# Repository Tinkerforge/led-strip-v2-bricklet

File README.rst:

LED Strip Bricklet 2.0
======================

This repository contains the firmware source code and the hardware design
files. The documentation generator configs can be found at
https://github.com/Tinkerforge/generators

Repository Content
------------------

software/:
 * examples/: Examples for all supported languages
 * build/: Compiled files
 * src/: Source code of firmware
 * Makefile: Makefile to build project

hardware/:
 * Contains KiCad project files and additionally schematics as PDF

datasheets/:
 * Contains datasheets for sensors and complex ICs that are used

Hardware
--------

The hardware is designed with the open source EDA Suite KiCad
(http://www.kicad.org). Before you are able to open the files,
you have to install the Tinkerforge kicad-libraries
(https://github.com/Tinkerforge/kicad-libraries). You can either clone
them directly in hardware/ or clone them in a separate folder and
symlink them into hardware/
(ln -s kicad_path/kicad-libraries project_path/hardware). After that you
can open the .pro file in hardware/ with KiCad and from there view and
modify the schematics and the PCB layout.

Software
--------

If you want to do your own Brick/Bricklet firmware development we highly
recommend that you use our build environment setup script and read the
tutorial (https://www.tinkerforge.com/en/doc/Tutorials/Tutorial_Build_Environment/Tutorial.html).

To compile the C code we recommend you to install the newest GNU Arm Embedded
Toolchain (https://launchpad.net/gcc-arm-embedded/+download).
You also need to install bricklib2 (https://github.com/Tinkerforge/bricklib2).

You can either clone it directly in software/src/ or clone it in a
separate folder and symlink it into software/src/
(ln -s bricklib_path/bricklib2 project_path/software/src/). Finally make sure to
have CMake installed (http://www.cmake.org/cmake/resources/software.html).

After that you can build the firmware by invoking make in software/.
The firmware (.zbin) can then be found in software/build/ and uploaded
with brickv (click button "Flashing" on start screen).

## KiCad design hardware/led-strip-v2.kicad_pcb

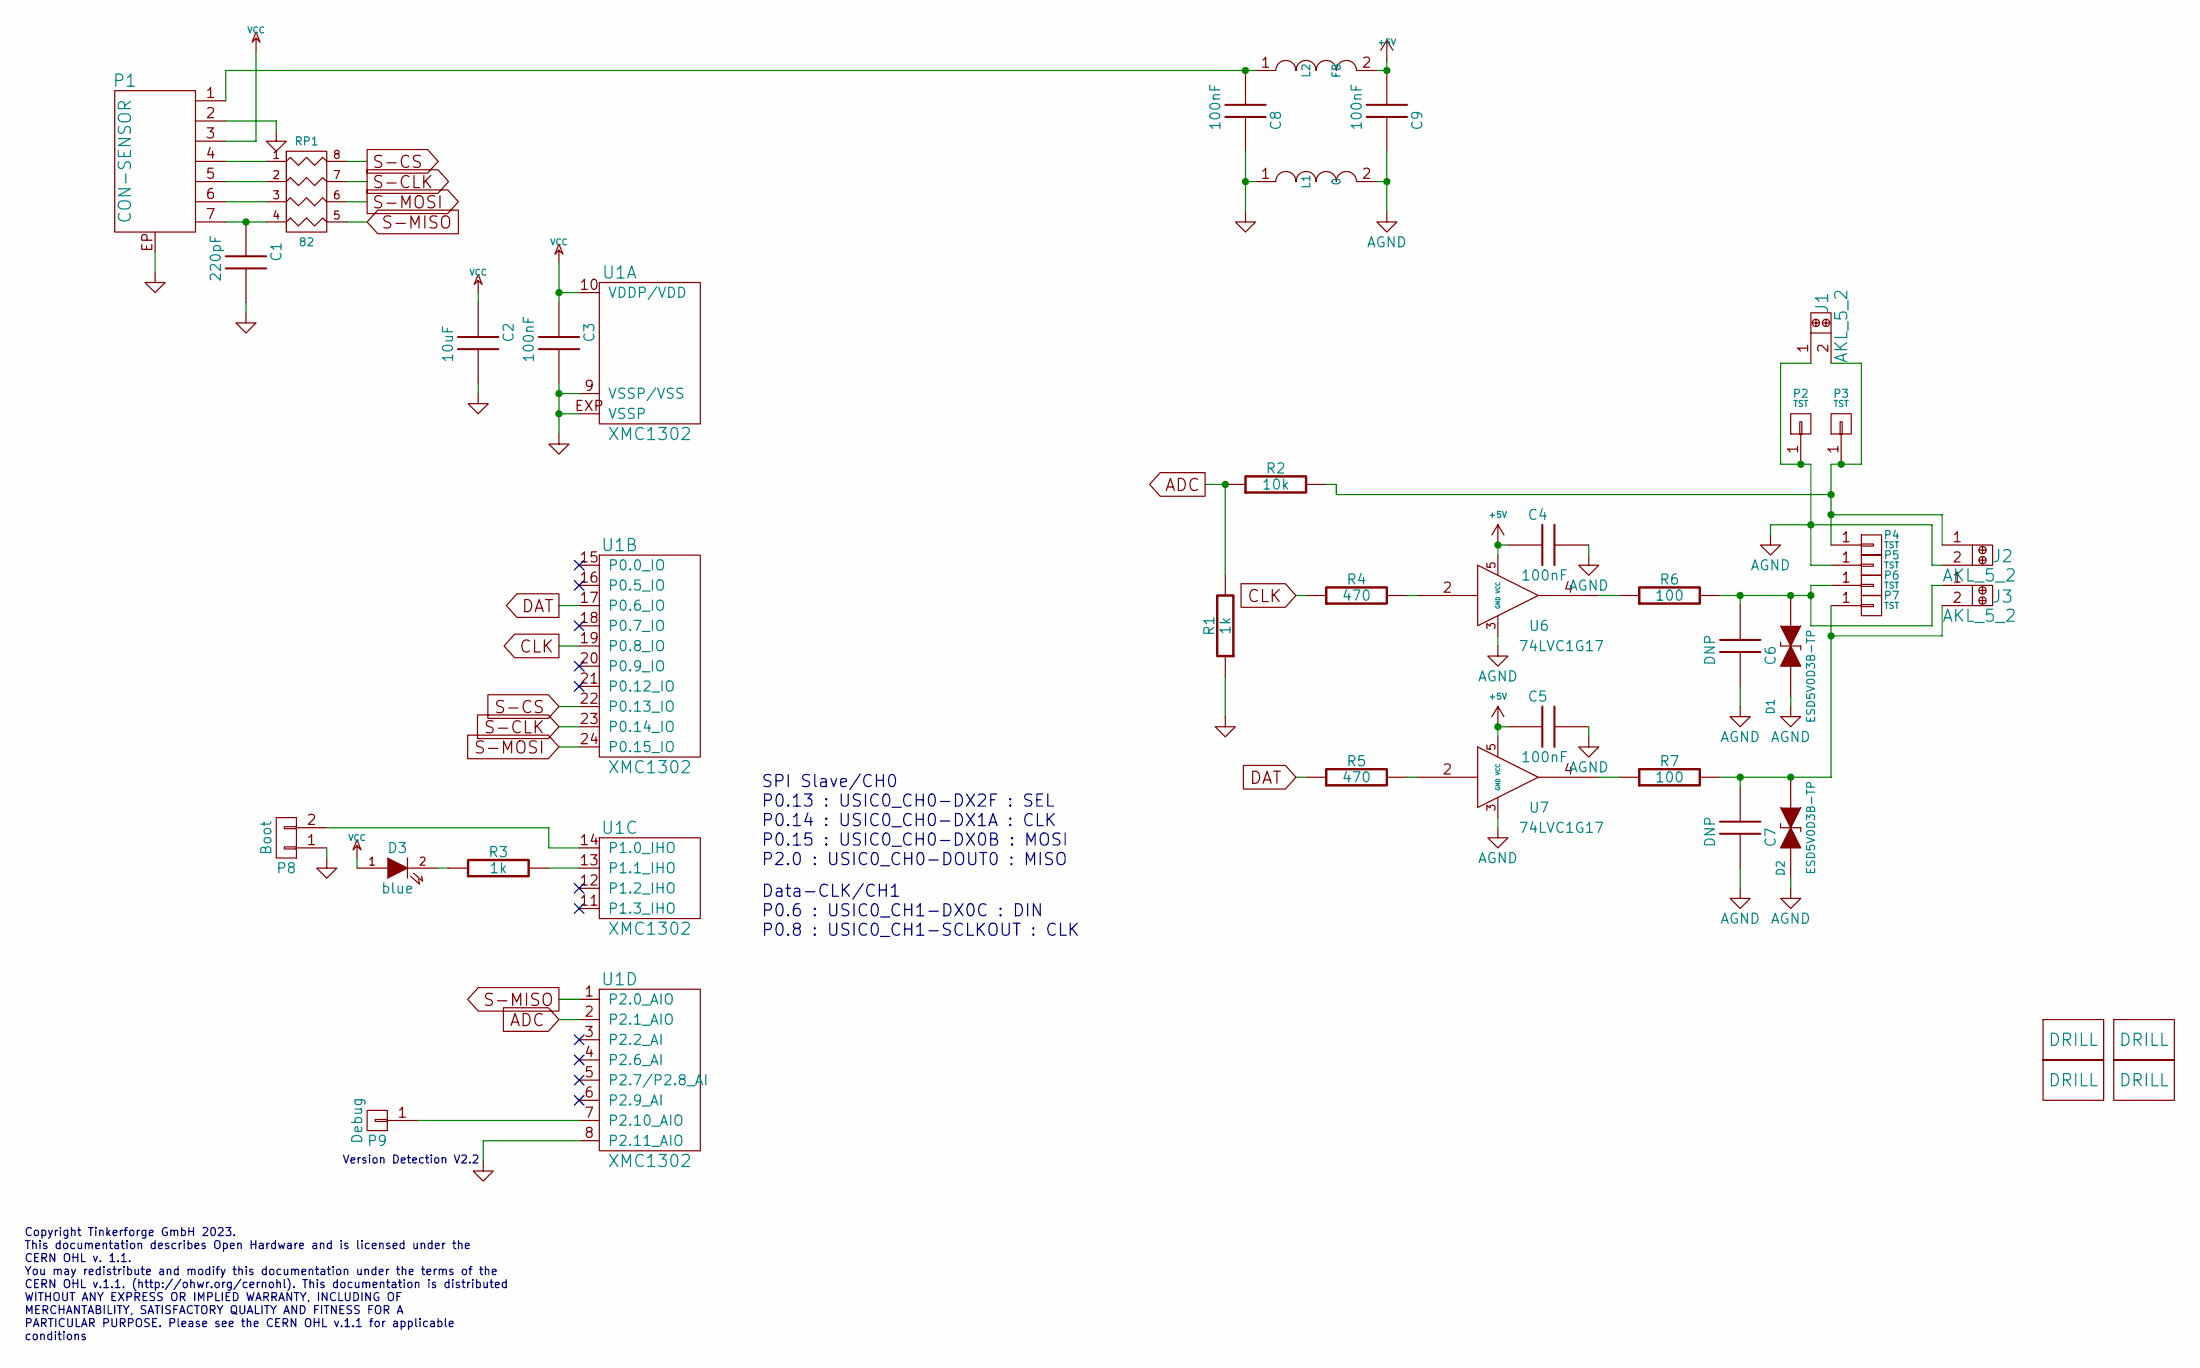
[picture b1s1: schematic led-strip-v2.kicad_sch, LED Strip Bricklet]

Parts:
C1: 220pF; C0402F
C2: 10uF; C0805E
C3, C4, C5, C8, C9: 100nF; C0603F
C6, C7: DNP; C0603F
D1, D2: ESD5V0D3B-TP; SOD-323
D3: blue; D0603F
J1, J2, J3: AKL_5_2
L1: 0; R0603F
L2: FB; R0603F
P1: CON-SENSOR; CON-SENSOR2
P2, P3, P4, P5, P6, P7: TST; SOLDER_PAD2
P8: Boot; SolderJumper
P9: Debug; DEBUG_PAD
R1, R3: 1k; R0603F
R2: 10k; R0603F
R4, R5: 470; R0603F
R6, R7: 100; R0603F
RP1: 82; 4X0402
U1: XMC1302; QFN24-4x4mm-0.5mm
U2, U3, U4, U5: DRILL; DRILL_NP
U6, U7: 74LVC1G17; SOT23-5

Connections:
+5V: C4.1, C5.1, C9.1, L2.2, U6.5 (VCC), U7.5 (VCC)
ADC: R1.2, R2.1, U1.2 (P2.1_AIO)
AGND: C4.2, C5.2, C6.2, C7.2, C9.2, D1.2 (K), D2.2 (K), J1.1, J2.2, L1.2, P2.1, P5.1, U6.3 (GND), U7.3 (GND)
CLK: R4.1, U1.19 (P0.8_IO)
DAT: R5.1, U1.17 (P0.6_IO)
GND: C1.2, C2.2, C3.2, C8.2, L1.1, P1.2, P1.EP, P8.1, R1.1, U1.8 (P2.11_AIO), U1.9 (VSSP/VSS), U1.EXP (VSSP)
unnamed: C1.1, P1.7, RP1.4
unnamed: C6.1, D1.1 (A), J3.1, P6.1, R6.2
unnamed: C7.1, D2.1 (A), J3.2, P7.1, R7.2
unnamed: C8.1, L2.1, P1.1
unnamed: D3.2 (K), R3.1
unnamed: J1.2, J2.1, P3.1, P4.1, R2.2
unnamed: P1.4, RP1.1
unnamed: P1.5, RP1.2
unnamed: P1.6, RP1.3
unnamed: P8.2, U1.14 (P1.0_IHO)
unnamed: P9.1, U1.7 (P2.10_AIO)
unnamed: R3.2, U1.13 (P1.1_IHO)
unnamed: R4.2, U6.2
unnamed: R5.2, U7.2
unnamed: R6.1, U6.4
unnamed: R7.1, U7.4
S-CLK: RP1.7 (R2), U1.23 (P0.14_IO)
S-CS: RP1.8 (R1), U1.22 (P0.13_IO)
S-MISO: RP1.5 (R4), U1.1 (P2.0_AIO)
S-MOSI: RP1.6 (R3), U1.24 (P0.15_IO)
VCC: C2.1, C3.1, D3.1 (A), P1.3, U1.10 (VDDP/VDD)

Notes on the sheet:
Copyright Tinkerforge GmbH 2023. This documentation describes Open Hardware and is licensed under the CERN OHL v. 1.1. You may redistribute and modify this documentation under the terms of the CERN OHL v.1.1. (http://ohwr.org/cernohl). This documentation is distributed WITHOUT ANY EXPRESS OR IMPLIE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
Version Detection V2.2
SPI Slave/CH0 P0.13 : USIC0_CH0-DX2F : SEL P0.14 : USIC0_CH0-DX1A : CLK P0.15 : USIC0_CH0-DX0B : MOSI P2.0 : USIC0_CH0-DOUT0 : MISO
Data-CLK/CH1 P0.6 : USIC0_CH1-DX0C : DIN P0.8 : USIC0_CH1-SCLKOUT : CLK

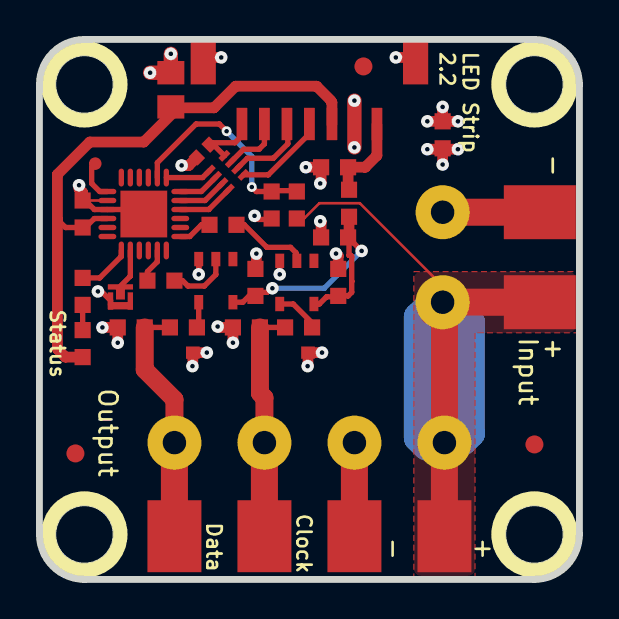
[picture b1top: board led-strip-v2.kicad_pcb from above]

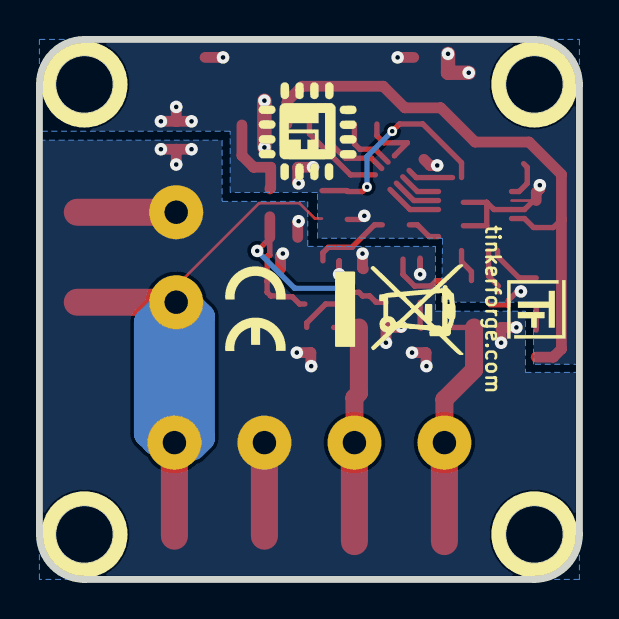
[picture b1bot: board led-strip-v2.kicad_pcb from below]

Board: 2 copper layers, 30.0 x 30.0 mm, 46 parts (2 on the bottom side), 27 nets.

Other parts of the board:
Fiducial_Mark: VAL**; Fiducial_Mark
Fiducial_Mark#2, Fiducial_Mark#3: VAL**; Fiducial_Mark
VAL: CE_5mm
VAL#2: WEEE_7mm

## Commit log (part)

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2018-01-11 add readme file
2018-01-12 add new hardware prototype
2018-01-15 change default via size
2018-02-15 specify processor
2018-02-15 Add datasheets
2018-02-15 Add gitignore
2018-02-15 Add firmware
2018-02-20 Cleanup KiCad libraries config
    Ensure LibDir=kicad-libraries and LibName1=tinkerforge.
    Remove special library.
2018-03-05 Remove unused flash-size define
2018-03-15 fix description text
2018-03-26 Make sure that LED type is updated during initialization
2018-04-16 Add 3d model (*.FCStd & *.step)
2018-05-04 Rename files
2018-05-04 Add schematic PDF
2018-05-30 remove solder paste layer of solder pads
2018-05-30 Add examples skeletons
2018-06-04 Fix get_values streaming logic
2018-06-04 Remove debug
2018-06-07 Fix indentation
2018-06-07 Update changelog for initial release
2018-06-11 Fix bit mixup in lookup table for WS281x LEDs
2018-06-13 Fix schematic filename
2018-06-18 Change capacitor footprint(s) to C0402F
2018-06-28 Fix readme
2018-07-11 Add Makefile with docker support
2018-07-11 Update directory structure and build instructions
2018-07-11 Remove obsolete generate_makefile scripts
2018-07-17 examples: Fix wrong callback name
2018-07-19 Fix typo
2018-10-04 Increase version for new release (changes in bricklib2)
2018-10-04 Add rev to changelog
2018-11-06 Add rust examples
2018-11-07 rust: Accept host names for ip connection, fix naming inconsistencies
2018-11-07 rust: Rename callback receivers.
2018-11-12 Fill in incomplete LED Strip V2 Python examples
2018-11-12 Add auto-generated simple examples
2018-11-28 c: Add missing stream length parameter
2018-12-14 Add go examples.
2018-12-18 go: Change import path.
2018-12-18 go: Change import path again.
2018-12-20 rust: Fix result variable names in examples.
2019-01-24 mqtt: Add examples.
2019-01-24 mqtt: Fix example header.
2019-01-24 mqtt: Remove executable bit in example permissions.
2019-01-24 go: Minor example fixes.
2019-03-28 mqtt: Fix whitespace.
2019-03-28 c: Examples: Pre-declare array used as parameter.
2019-05-14 Update rust examples.
2019-05-29 Dont disable post calibration
2019-08-22 c: Adapt to bindings changes
2019-11-20 Rewrite get_led_values. Fix streaming.
2019-11-20 Increase version for new release.
2019-11-20 Add rev to changelog.
2019-11-20 Add more details to changelog
2019-11-20 Fine-tune changelog
2020-01-13 examples: Use python3 input instead of python2 raw_input.
2020-01-14 examples: Use python3 input by default.
2020-03-16 python: Fix comment
2020-03-16 Whitespace
2020-03-16 go,mqtt,rust: Update to new example skeleton
2020-03-18 delphi: Avoid keywords
2020-04-03 Add openHAB examples.
2020-04-03 Fix openhab example file extension.
2020-06-10 version 2.1, improve ground connection
2020-08-04 specify fuse
2020-08-19 Add uc examples.
2020-08-25 uc: Fix whitespace
2020-08-25 uc: Adapt examples to new skeleton
2020-08-27 uc: Fix warnings.
2020-09-02 uc: Add example driver note.
2021-10-25 Update KiCad link
    https://www.kicad.org/blog/2021/10/Avoid-links-to-former-kicad-domain/
2022-04-19 examples: uc: Rename TF_HalContext to TF_HAL.
2022-04-26 uc: Adapt to bindings changes
2022-07-06 Add license files.
2022-08-23 add 2.2 data
2022-09-21 add version detection pin to pcb
2023-01-23 New standart layout. Switched to Kicad 6
2023-01-25 Data Cleanup
2023-07-28 update to kicad 7. updated schematic version v2.2 detection. updatet schematic pdf
2023-07-28 Add support for hardware version 2.2
2023-07-28 Add ref for 2.0.4
2023-09-01 Fix version in changelog
2025-10-04 Fix compatibility with new Docker build image (GCC 14.2.1)

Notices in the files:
hardware/led-strip-v2.kicad_pcb:
Licensed under CERN OHL v.1.1
Copyright (©) 2023, B.Nordmeyer
